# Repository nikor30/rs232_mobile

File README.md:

# RS232-WLAN-Konsole

Mobiler serieller Konsolenserver auf ESP32-Basis: mit dem WLAN-Hotspot des Geräts verbinden, `http://192.168.4.1` öffnen, Terminal auf Switch, Router oder Firewall. Keine App, kein Treiber, kein USB-Seriell-Adapter — und auf Wunsch aus der Ferne über die Leitstelle.

Firmware-Stand: **v1.8.2** · Board: **Waveshare ESP32-S3-Touch-LCD-2** · Oberflächen auf Englisch, Deutsch und Portugiesisch

## Was es kann

| Wo | Was |
|---|---|
| **Am Gerät** | Touch-Display mit Portstatus, Baudrate, Auto-Baud, BREAK, Terminal und Skripten; Akku mit Ladeanzeige und Sparmodus |
| **Im Browser** | xterm.js-Terminal über den eigenen Hotspot oder das Firmennetz, ohne Installation — am Handy wie am Notebook |
| **Im Netz** | Raw-TCP und Telnet je Port (PuTTY), Bluetooth-LE-Konsole, XMODEM/YMODEM, 802.1X (PEAP, TTLS, EAP-TLS), HTTPS |
| **Auf der SD-Karte** | Mitschnitte je Port, gespeicherte Konfigurationen zum Abspielen, verschlüsselte Sicherung; die Karte lässt sich als USB-Stick verleihen |
| **Aus der Ferne** | Leitstelle mit Geräteübersicht, Fernkonsole Ende-zu-Ende verschlüsselt, Firmware-Updates nur signiert (ML-DSA-65), Images auf die SD-Karte |

<table>
  <tr>
    <td align="center" width="38%"><br><sub>Touch-Display am Gerät</sub></td>
    <td align="center"><br><sub>Weboberfläche des Geräts am Handy</sub></td>
  </tr>
</table>

## Leitstelle

Geräte melden sich ausgehend per HTTPS bei einem Server — kein offener Port am Gerät, kein VPN. Der Kanal darin ist hybrid verschlüsselt (X25519 + ML-KEM-768); angemeldet wird mit einem sechsstelligen Code vom Display. Konten mit Passwort und Authenticator-App, Gruppen mit Rechten, Standorte, eine Bibliothek für Vorlagen, Firmware und Images.

Die **Fernkonsole** braucht einen Tipp am Gerät (oder eine dort gesetzte Frist für unbeaufsichtigten Zugriff), läuft höchstens 60 Minuten und ist Ende-zu-Ende verschlüsselt: Der Server trägt nur Chiffretext, Display und Browser zeigen denselben Code. Skripte lassen sich im Terminal abspielen, Sitzungen in eine Textdatei aufzeichnen.

## Hardware (Entwurf)

Eine Trägerplatine für das Waveshare-Modul mit **vier galvanisch getrennten RS232-Ports auf RJ45** (Cisco-Belegung; je Port Optokoppler, MAX3232E und eigener isolierter Wandler, aus dem Akku schaltbar) und ein druckbares Gehäuse. Entworfen und per KiCad-DRC geprüft, **noch nicht gebaut** — Quellen, Gerber für PCBWay und STL-Dateien im Zweig [`hardware-carrier`](../../tree/hardware-carrier/hardware).

<table>
  <tr>
    <td align="center"><br><sub>Trägerplatine 78 × 107 mm</sub></td>
    <td align="center"><br><sub>Körper, Platine, Boden</sub></td>
  </tr>
</table>

Heute läuft das Gerät mit einem MAX3232-Modul an einem Port, geprüft an Cisco C3750-X und C2960CX.

## Aufbau

- [`HANDOVER.md`](HANDOVER.md) — Projektstand, Erfahrungswissen, offene Punkte
- [`firmware/`](firmware/) — PlatformIO-Projekt für das Waveshare ESP32-S3-Touch-LCD-2 ([Weboberfläche und Netz](firmware/README.md), [Board](firmware/WAVESHARE.md))
- [`server/`](server/) — Leitstelle (Command-and-Control-Server) in Go: [Konzept](server/KONZEPT.md), [Betrieb und Admin-API](server/README.md)
- [`tests/`](tests/) — Host-Unittests der Firmware und Protokolltests gegen den Server

```bash
cd firmware
pio run -t upload                          # Englisch
pio run -e waveshare-s3-lcd2-de -t upload  # Deutsch (-pt: Portugiesisch)

cd server
docker compose up -d --build               # Leitstelle lokal, siehe server/README.md
```

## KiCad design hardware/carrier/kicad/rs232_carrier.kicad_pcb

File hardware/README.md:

# Hardware: Trägerplatine mit vier galvanisch getrennten RS232-Ports und Gehäuse

Stand 27. Oktober 2026, Revision 0.3 (Modul mittig, Gehäuse aus Körper und Boden) — **entworfen und per KiCad-DRC geprüft, noch nicht gebaut.**
Vor der Bestellung die Liste unter „Vor der Bestellung prüfen“ abarbeiten.

## Was es ist

Eine Trägerplatine (78 × 107 mm, zweilagig), auf die das **Waveshare ESP32-S3-Touch-LCD-2** mit seinen
beiden 14-poligen Stiftleisten gesteckt wird. Das Modul bringt Display, Touch, Lagesensor (QMI8658),
SD-Slot, LiPo-Lader und USB-C mit; die Trägerplatine ergänzt:

- **vier RS232-Ports auf RJ45** (Cisco-Konsolenbelegung: Pin 3 TX, Pin 6 RX, Pin 4/5 GND), jeder Port
  galvanisch getrennt — zwei Optokoppler **TLP2361** (10 MBd, einer je Richtung), ein **MAX3232E** und ein
  eigener isolierter 1-W-Wandler **B0505S-1WR3** (1,5 kV). Die vier Inseln sind auch voneinander getrennt.
- **Versorgung der Ports aus dem Akku**: VBAT → Aufwärtswandler MT3608 (5,1 V) → je Port ein High-Side-Schalter
  (2N7002 + AO3401), den die Firmware über GPIO16/17/18/10 schaltet. Ein abgeschalteter Port zieht nichts;
  ein eingeschalteter Port kostet rund 30–40 mA am Akku (Wandler im Leerlauf + MAX3232 + LED).
- **Lötbrücken** je Port, um TX/RX an der Buchse zu tauschen (JPx01/JPx02), und je Port eine Lötbrücke,
  ob der Port ohne Firmware-Unterstützung dauerhaft versorgt wird (JP11–JP14, Brücke 2-3 = immer an).
- Akku liegt **unter** der Trägerplatine im Gehäuse hinter einer Klappe und steckt an einer JST-PH-Buchse (J4) auf der
  Unterseite der Trägerplatine; BAT+ erreicht das Modul über Pin 14 (VBAT) der Stiftleiste. Falls dieser Pin nicht der
  Zellenanschluss ist (prüfen!), bleibt der Schlitz für ein Kabel zum MX1.25-Anschluss des Moduls.
- Stecker J3: 3V3, GND, I²C (GPIO47/48) und GPIO2/4/6 für spätere Erweiterungen.

Der Lagesensor für die automatische Drehung sitzt auf dem Modul; auf der Trägerplatine ist dafür nichts nötig.

### Externe Antenne

Das Modul hat eine Keramikantenne; das Bauteilfoto von Waveshare zeigt keine IPEX-Buchse, die
Schwesterboards haben eine mit 0-Ω-Umschaltwiderstand — am Modul nachsehen. Das Gehäuse hat links eine Bohrung (6,5 mm) für eine
RP-SMA-Einbaubuchse; ein U.FL/IPEX-Pigtail von dort zum Modul. **Am Modul nachsehen**, ob eine IPEX-Buchse
bestückt ist; wenn nicht, bleibt nur die Keramikantenne (das Gehäuse setzt sie an die linke, metallfreie Seite,
rund 50 mm von den RJ45-Buchsen entfernt).

## Verzeichnis

| Pfad | Inhalt |
|---|---|
| `carrier/generate.py` | **Die Quelle.** Erzeugt Schaltplan, Platine, Projekt, DRC-Regeln, `bom.csv` und `preview.png`. Alle Maße stehen hier (`VERIFY`, Platzierungen). |
| `carrier/kigen.py` | Schreiber für KiCad-7-Dateien (Symbole, Footprints, eingebettet — keine Bibliothek nötig) |
| `carrier/route.py` | Eigener Gitter-Autorouter (zwei Lagen, Vias, netzklassen-abhängige Abstände, Rip-up) |
| `carrier/drc.py` | Zonen füllen, KiCad-DRC, Fertigungsdaten exportieren (`kicad/fab/`) |
| `carrier/kicad/` | KiCad-7-Projekt: `rs232_carrier.kicad_pro/.kicad_sch/.kicad_pcb`, `channel.kicad_sch` (ein Port, viermal eingebunden), `.kicad_dru` |
| `carrier/kicad/fab/` | **Gerber + Bohrdaten als ZIP für PCBWay**, Bestückungsdaten (`-pos.csv`), Schaltplan-PDF, Platinen-PDF, DRC-Bericht |
| `carrier/bom.csv` | Stückliste mit Vorschlägen für Bauteile |
| `carrier/render3d.py` | Bestückte Platine als 3D-Ansicht von oben und unten (`kicad/fab/rs232_carrier-3d-*.png`), aus den Footprint-Maßen, ohne Herstellermodelle |
| `enclosure/generate_enclosure.py` | Erzeugt `rs232_console_case.scad` aus denselben Maßen und rendert die STL-Dateien |
| `enclosure/body.stl`, `base.stl` | Körper und Bodenplatte zum Drucken; `preview_*.png` zur Ansicht |

Neu erzeugen (KiCad 7 und OpenSCAD müssen installiert sein):

```bash
cd hardware/carrier && python3 generate.py && python3 route.py && python3 drc.py
cd ../enclosure && python3 generate_enclosure.py
```

`generate.py` ist deterministisch (feste UUIDs); Änderungen an Maßen oder Bauteilen dort eintragen, nicht in
den KiCad-Dateien — die werden überschrieben. Wer lieber in KiCad weiterarbeitet, nimmt die erzeugten Dateien
als Ausgangspunkt und lässt den Generator danach in Ruhe.

## Pinbelegung am Modul

| Port | RX (ESP-Eingang) | TX (ESP-Ausgang) | Versorgung an |
|---|---|---|---|
| 1 | GPIO44 | GPIO21 | GPIO16 |
| 2 | GPIO15 | GPIO13 | GPIO17 |
| 3 | GPIO11 | GPIO12 | GPIO18 |
| 4 | GPIO14 | GPIO9 | GPIO10 |

Port 1 behält die bisherige Belegung (RX 44 / TX 21). GPIO43 (U0TXD) bleibt frei, weil das ROM beim Reset dort
schreibt. Die TX-LED des Optokopplers liegt zwischen 3V3 und dem GPIO (Katode am GPIO): während des Resets ist
der Pin hochohmig, die LED aus, die RS232-Leitung in Ruhe — **beim Reset erscheint nichts auf dem Sendepin.**
Das Häkchen „RX/TX tauschen“ der Firmware darf mit dieser Platine nicht gesetzt werden (die Optokoppler haben
eine feste Richtung; 100 Ω in der RX-Leitung begrenzen den Strom, falls es doch passiert).

Firmware (geändert in diesem Stand, **nicht kompiliert und nicht am Gerät geprüft**):
`config.h` (Pin-Freigabe, `PINS_PORT_EN`), `serial_bridge.cpp/.h` (`portPower()`, `allPortsOff()`),
`lcd_ui.cpp` (Versorgungen vor dem Tiefschlaf aus und gehalten, nach dem Aufwachen freigegeben).
Ein aktivierter Port bekommt beim Start seine Versorgung, deaktivierte Ports bleiben stromlos.

## Signalweg eines Ports

```
ESP GPIO (TX) ─330Ω/LED─▶ TLP2361 ─▶ T1IN  MAX3232E  T1OUT ─JP01─▶ RJ45 Pin 3
ESP GPIO (RX) ◀─100Ω──── TLP2361 ◀─ 74LVC1G17 ◀─ R1OUT   R1IN ◀─JP02─ RJ45 Pin 6
                 3V3-Seite  ║ 1,5 kV ║  ISO5V-Seite (B0505S aus dem geschalteten 5 V)
```

Beide LEDs sind in Ruhe (UART-Mark) aus, also kein Ruhestrom durch die Koppler. Der Schmitt-Puffer treibt die
RX-LED, weil der Empfängerausgang des MAX3232 dafür zu schwach ist.

## Mechanik und Gestaltung

Leitlinie (Rams, Ive): ein ruhiger Körper mit durchlaufenden Radien, symmetrische Flächen, außen nur, was
täglich gebraucht wird, keine sichtbaren Schrauben, Fugen nur dort, wo man sie nicht sieht.

- Modul **hochkant und mittig** auf der Trägerplatine, 11 mm darüber: USB-C in der Mitte der oberen Stirnseite,
  die Nadellöcher für BOOT/RST symmetrisch daneben, die Antenne des Moduls zeigt zu den Ports. Links vom Modul
  der Aufwärtswandler mit den Entkoppeldioden, rechts die vier Portschalter, darunter die vier Inseln und die
  RJ45-Reihe — die Platine ist um ihre Mittellinie symmetrisch aufgeteilt.
- **Das Displayglas ist die Oberseite** (bündig, 0,15 mm Spiel im Rahmen; der Rahmen ist zur USB-C-Seite
  offen, die Stirnwand liegt unter dem Glasüberstand). Über den Buchsen sind die Ziffern 1–4 in die Oberseite
  vertieft (0,4 mm) — die einzige Beschriftung.
- **Zwei gedruckte Teile, keine Schraube** (`enclosure/`):
  - `body.stl` — der ganze Körper: Oberseite mit Glasrahmen und alle vier Wände bis zur Unterkante, Ecken
    R 5, Kanten R 1,2. Öffnungen: vier geschlossene Fenster für die RJ45 (die Buchsen sitzen 0,6 mm hinter
    der Platinenkante, also ganz in der Wand), eine Mulde für USB-C, zwei Nadellöcher (1,5 mm), die
    RP-SMA-Bohrung rechts oben an der Seitenwand. Innen vier Pfosten, die die Trägerplatine auf die Zapfen
    des Bodens drücken, und eine Nut, in die die Haken des Bodens greifen.
  - `base.stl` — Bodenplatte, **liegt innen in den Wänden**, 0,6 mm zurückgesetzt: die Fuge ist nur von unten
    zu sehen. Sechs Rasthaken (10 × 1,6 × 6 mm, 0,8 mm Nase, 30° Einführ-, 45° Haltewinkel, Wurzelradius
    0,8 mm) klicken in die Nut; zwei Kerben in der Unterkante nehmen einen Fingernagel oder Spatel zum Öffnen.
    Acht Zapfen tragen die Trägerplatine (Schulter 5,5 mm, Stift 2,4 bzw. 1,9 mm durch die Bohrungen),
    ein 1,5 mm hoher Rahmen hält den Akku (bis 60 × 70 × 6 mm) an seinem Platz, vier Vertiefungen für
    8-mm-Gummifüße, Schriftzug vertieft. Boden abziehen = Akku wechseln (Stecker J4 auf der Unterseite der
    Trägerplatine), ohne Werkzeug.
- Einbau: Trägerplatine mit Modul von unten in den Körper schieben (die Buchsen fahren in ihre Fenster, das
  Glas in den Rahmen), Boden mit Akku aufsetzen, bis die sechs Haken klicken.
- Nicht nach außen geführt: der SD-Slot (sitzt beim mittigen Modul 22 mm von der Wand; die Karte bleibt
  eingebaut, Zugriff über den USB-Stick-Modus oder nach Abnehmen des Bodens).
- Außen **83 × 114 × 31 mm**. Drucken: Körper mit der Oberseite nach unten (Pfosten wachsen nach oben, der
  Glasrahmen wird glatt), Boden flach (Haken wachsen nach oben); PETG oder ABS, nicht PLA. Farbe nach Rams:
  helles Warmgrau oder Anthrazit, matt. Regeln aus den FDM-Leitfäden (Hubs, Formlabs, Core77): Spiel 0,3 mm,
  Hakenlänge ≈ 4 × Dicke mit Wurzelradius, in Z gedruckte Haken dicker als flach gedruckte. **Erster Druck als
  Probe**: Haken und Nut sind nicht gedruckt worden; Spiel ggf. in `generate_enclosure.py` (`clr`,
  `hook_catch`) anpassen.
- Isolationsabstand auf der Platine: 5 mm kupferfreies Band zwischen ESP-Seite und Inseln (DRC-Regel 3 mm),
  1,8 mm zwischen den Inseln (DRC-Regel 1,5 mm). Unter den Zapfen/Pfosten ist das Kupfer ausgespart.

## Bestellen bei PCBWay

Datei `carrier/kicad/fab/rs232_carrier-gerbers-pcbway.zip` hochladen. Einstellungen: 2 Lagen, 78 × 107 mm,
FR-4 1,6 mm, 1 oz Kupfer, Lötstopplack beliebig, HASL bleifrei oder ENIG, kleinste Leiterbahn/Abstand
0,25/0,2 mm (Mindestwerte der Platine: 0,25 mm Bahn, 0,2 mm Abstand, Via 0,7/0,3 mm). Keine besonderen
Anforderungen. Für Bestückung durch PCBWay: `rs232_carrier-pos.csv` und `bom.csv` (Bauteile dort ergänzen).

## Vor der Bestellung prüfen

Die Maße des Waveshare-Moduls stammen aus der offiziellen Maßzeichnung (Platine 35,00 × 48,20 mm, vier
Bohrungen 29,00 × 42,20 mm im Abstand 3,00 mm von den Kanten, Glas 37,10 × 58,80 mm mit R2,60, Stapel
9,70 mm gesamt bzw. 7,20 mm von der Glasoberseite bis zur Platinenunterseite, Stiftleisten 30,48 mm
auseinander, USB-C mittig). Alles steht in `carrier/generate.py` unter `VERIFY`; nach einer Korrektur die
drei Skripte neu laufen lassen.

1. **Lage von Pin 1** der Stiftleisten in Längsrichtung (7,3 mm vom USB-C-fernen Rand, aus der Zeichnung
   abgeleitet, nicht bemaßt). Ein Fehler von mehr als 0,3 mm und das Modul passt nicht in die Buchsen —
   vor dem Einlöten der Buchsenleisten mit dem Modul abgleichen.
2. **Glasüberstand**: Das Glas (58,80 mm) ist 10,6 mm länger als die Platine (48,20 mm); angenommen ist je
   5,3 mm Überstand an beiden kurzen Seiten und 1,05 mm an den langen. Die Zeichnung bemaßt den Überstand
   nicht getrennt — am Modul nachmessen, sonst stimmt das Gehäusefenster nicht.
3. **Stapelhöhe** 11 mm (Buchsenleiste 8,5 mm + Stiftleistenkörper 2,5 mm) und Glasoberkante 5,6 mm über
   der Modulplatine (7,20 − 1,60 aus der Seitenansicht). Bestimmt, ob das Glas bündig mit dem Körper
   abschließt; mit 1-mm-Unterlegscheiben unter den Buchsenleisten lässt sich das ausgleichen.
4. **RJ45-Buchse**: Der Footprint `RJ45_Generic` ist ein Platzhalter (Pins 1,27 mm Raster, zwei Reihen 2,54 mm,
   Zapfen 3,25 mm im Abstand 11,43 mm). Vor der Bestellung die Buchse festlegen (z. B. Amphenol 54602-908LF
   oder RJHSE-5380) und den Footprint in `generate.py` an deren Datenblatt anpassen — oder in KiCad den
   Bibliotheks-Footprint zuweisen. Pin 1 ist links, wenn man von vorn in die Buchse sieht, die Rastnase unten.
5. **B0505S-1WR3**: Pins auf 0 / 2,54 / 10,16 / 12,7 mm, Pin 1 = −Vin. Im Datenblatt gegenprüfen.
6. **TLP2361**: Pin 1 Anode, 3 Katode, 4 GND, 5 Ausgang, 6 Vcc (Pin 2 fehlt). Ebenso für ACPL-M61L.
   LED-Vorwiderstände (330 Ω / 680 Ω ≈ 5 mA) an den gewählten Typ anpassen.
7. **MT3608**: Vout = 0,6 V · (1 + 75k/10k) = 5,1 V — innerhalb der 4,5–5,5 V des B0505S.
8. **Spule** L1: Footprint ist ein generisches 5 × 5 mm mit zwei Pads; Bauteil mit ≥ 1 A Sättigungsstrom.
9. **Antenne**: IPEX-Buchse am Modul vorhanden? Sonst SMA-Bohrung verschließen.
10. **VBAT an Pin 14 der Stiftleiste**: Mit dem Multimeter prüfen, dass der Pin direkt mit BAT+ des MX1.25-Anschlusses
    verbunden ist (0 Ω). Nur dann lädt und versorgt der Akku an J4 das Modul über die Stiftleiste. Sonst ein kurzes
    Kabel von J4 durch den Schlitz zum MX1.25-Anschluss ziehen und J4 nicht bestücken.
11. **USB-C-Überstand** des Moduls (angenommen 1,9 mm über die Platinenkante) — bestimmt den Abstand der
    Stirnwand zur Modulkante.

Was sonst noch offen ist: Die Firmwareänderung ist ungetestet (kein PlatformIO in der Sandbox); die
Optokoppler-Schaltung ist nach Datenblattwerten ausgelegt, nicht gemessen; der Autorouter hat keine
Längen- oder Impedanzregeln (bei 115 200 Baud belanglos). Die Silkscreen-Warnungen des DRC (Texte
überlappen Bauteilumrisse) sind kosmetisch.

## Entscheidungen

- **Trägerplatine statt eigener Hauptplatine**: Die Firmware ist auf dieses Modul (Display, Touch, SD,
  Lagesensor, Lader) eingerichtet; ein Nachbau dieser Funktionen auf einer eigenen Platine wäre ein
  Vielfaches an Aufwand ohne Nutzen. Nachteil: die Antenne bleibt die des Moduls.
- **RJ45 statt DB9**: Vier DB9 wären 130 mm breit. Mit der Cisco-Belegung passt das vorhandene blaue
  Rollover-Kabel direkt an Cisco/HP/Juniper-Konsolen; an DB9-Geräte kommt man mit dem üblichen
  RJ45-DB9-Adapter des Kabelsatzes. Wer eine andere Belegung braucht, lötet JPx01/JPx02 um.
- **Optokoppler statt digitaler Isolatoren** (Wunsch): TLP2361 ist mit 10 MBd und 2,7–5,5 V Versorgung
  für beide Seiten geeignet; ein ADuM1201 wäre kleiner und ohne LED-Strom, aber eine andere Schaltung.
- **Ein Wandler je Port** statt einem gemeinsamen: nur so sind die Ports auch untereinander getrennt
  (zwei Geräte mit verschiedenem Erdpotential gleichzeitig).
- **Schaltbare Versorgung**: Die vier Wandler zögen sonst dauerhaft 30–60 mA; am 1000-mAh-Akku wären das
  Stunden. Standard ist „aus“ (Pull-down), die Firmware schaltet ein.
- **Abstände**: 19 mm Portraster, weil 17,5/18 mm für Ladungspumpen-Kondensatoren, MAX3232 und Wandler in
  einer Spalte nicht reichten — die Platine wurde dafür von 72 auf 78 mm breiter; mit dem hochkant stehenden
  Modul (Wunsch: USB-C an der Stirnseite, Glas als Oberseite) 107 mm lang.
- **Zusammenstecken statt Schrauben** (Wunsch): Körper und innenliegender Boden mit sechs lösbaren Haken; die
  Trägerplatine ist zwischen Zapfen und Pfosten geklemmt. Boden ab = Akku zugänglich (J4 auf der Platinenunterseite).
- **Modul mittig** (Wunsch): Versorgung links und rechts aufgeteilt; dafür ist der SD-Slot nicht mehr von außen
  erreichbar — die Karte bleibt eingebaut.

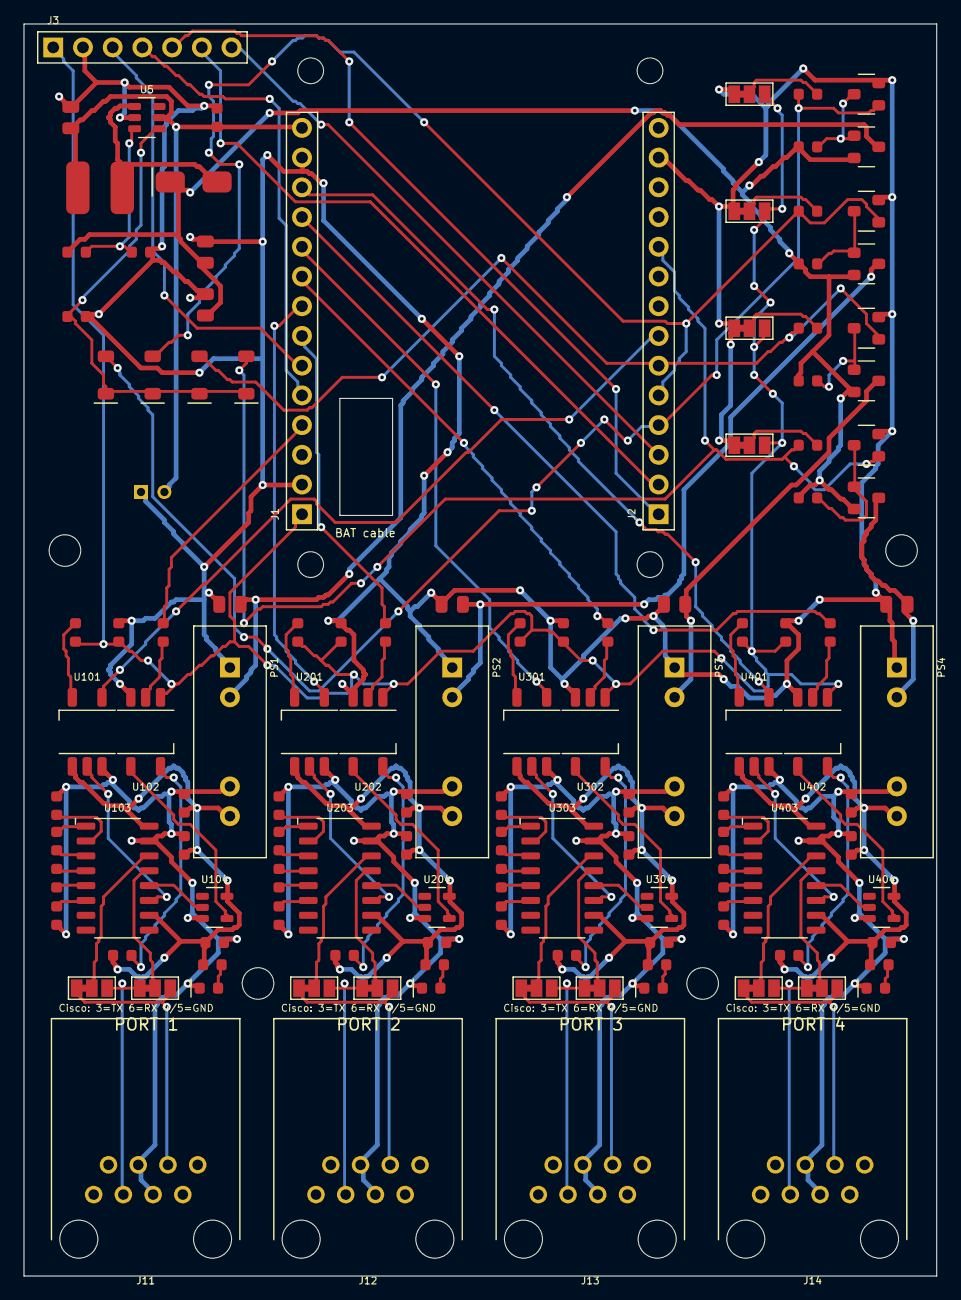
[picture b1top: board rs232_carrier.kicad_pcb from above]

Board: 2 copper layers, 78.0 x 107.0 mm, 134 parts (1 on the bottom side), 112 nets.

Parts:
C51: 10u; C_0805
C52, C53: 22u; C_0805
C54, C101, C102, C103, C104, C105, C107, C108, C201, C202, C203, C204, C205, C207, C208, C301, C302, C303, C304, C305, C307, C308, C401, C402, C403, C404, C405, C407, C408: 100n; C_0603
C109, C209, C309, C409: 4.7u; C_0603
C110, C210, C310, C410: 2.2u; C_0805
D5: SS14; D_SMA
D51, D52, D53, D54: 1N4148W; D_SOD-123
D101, D201, D301, D401: LED green; LED_0603
H1, H2, H3, H4: M2 Waveshare; MountingHole_2.2
H5, H6, H7, H8: M2.5 enclosure; MountingHole_2.7
J1: WS header 1-14; PinSocket_1x14
J2: WS header 15-28; PinSocket_1x14_B
J3: EXT; PinHeader_1x7
J4: BAT JST-PH; JST_PH_2_Vertical
J11, J12, J13, J14: RJ45; RJ45_Generic
JP11: EN1 dflt; SolderJumper_3_Bridged12
JP12: EN2 dflt; SolderJumper_3_Bridged12
JP13: EN3 dflt; SolderJumper_3_Bridged12
JP14: EN4 dflt; SolderJumper_3_Bridged12
JP101, JP201, JP301, JP401: TX->3; SolderJumper_3_Bridged12
JP102, JP202, JP302, JP402: RX<-6; SolderJumper_3_Bridged12
L1: 22u; L_5x5
PS1, PS2, PS3, PS4: B0505S-1WR3; SIP-4_DCDC
Q11, Q21, Q31, Q41: 2N7002; SOT-23
Q12, Q22, Q32, Q42: AO3401A; SOT-23
R51: 75k; R_0603
R52, R61, R62, R63, R64: 10k; R_0603
R53, R71, R72, R73, R74: 100k; R_0603
R101, R201, R301, R401: 330; R_0603
R102, R202, R302, R402: 680; R_0603
R103, R203, R303, R403: 100; R_0603
R104, R204, R304, R404: 2k2; R_0603
U5: MT3608; SOT-23-6
U101, U102, U201, U202, U301, U302, U401, U402: TLP2361; SO6_Opto
U103, U203, U303, U403: MAX3232E; SOIC-16
U104, U204, U304, U404: 74LVC1G17; SOT-23-5

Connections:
+3V3: C107.1, C207.1, C307.1, C407.1, J1.1, J3.1, JP11.3, JP12.3, JP13.3, JP14.3, R101.1, R201.1, R301.1, R401.1, U102.6, U202.6, U302.6, U402.6
+5V: C52.1, C53.1, D5.1, Q12.2, Q22.2, Q32.2, Q42.2, R51.1, R71.1, R72.1, R73.1, R74.1
/CH1/BUF_OUT: U102.3, U104.4
/CH1/C1N: C101.2, U103.3
/CH1/C1P: C101.1, U103.1
/CH1/C2N: C102.2, U103.5
/CH1/C2P: C102.1, U103.4
/CH1/ISO5V: C105.1, C108.1, C109.1, PS1.4, R102.1, R104.1, U101.6, U103.10, U103.16, U104.5
/CH1/ISOGND: C103.2, C104.2, C105.2, C108.2, C109.2, D101.1, J11.4, J11.5, PS1.3, U101.4, U103.15, U104.3
/CH1/LEDA: D101.2, R104.2
/CH1/R1IN: JP102.2, U103.13
/CH1/R1OUT: U103.12, U104.2
/CH1/RJ3: J11.3, JP101.1, JP102.3
/CH1/RJ6: J11.6, JP101.3, JP102.1
/CH1/RXA: R102.2, U102.1
/CH1/RX_O: R103.1, U102.5
/CH1/T1IN: U101.5, U103.11
/CH1/T1OUT: JP101.2, U103.14
/CH1/TXA: R101.2, U101.1
/CH1/VN: C104.1, U103.6
/CH1/VP: C103.1, U103.2
/CH2/BUF_OUT: U202.3, U204.4
/CH2/C1N: C201.2, U203.3
/CH2/C1P: C201.1, U203.1
/CH2/C2N: C202.2, U203.5
/CH2/C2P: C202.1, U203.4
/CH2/ISO5V: C205.1, C208.1, C209.1, PS2.4, R202.1, R204.1, U201.6, U203.10, U203.16, U204.5
/CH2/ISOGND: C203.2, C204.2, C205.2, C208.2, C209.2, D201.1, J12.4, J12.5, PS2.3, U201.4, U203.15, U204.3
/CH2/LEDA: D201.2, R204.2
/CH2/R1IN: JP202.2, U203.13
/CH2/R1OUT: U203.12, U204.2
/CH2/RJ3: J12.3, JP201.1, JP202.3
/CH2/RJ6: J12.6, JP201.3, JP202.1
/CH2/RXA: R202.2, U202.1
/CH2/RX_O: R203.1, U202.5
/CH2/T1IN: U201.5, U203.11
/CH2/T1OUT: JP201.2, U203.14
/CH2/TXA: R201.2, U201.1
/CH2/VN: C204.1, U203.6
/CH2/VP: C203.1, U203.2
/CH3/BUF_OUT: U302.3, U304.4
/CH3/C1N: C301.2, U303.3
/CH3/C1P: C301.1, U303.1
/CH3/C2N: C302.2, U303.5
/CH3/C2P: C302.1, U303.4
/CH3/ISO5V: C305.1, C308.1, C309.1, PS3.4, R302.1, R304.1, U301.6, U303.10, U303.16, U304.5
/CH3/ISOGND: C303.2, C304.2, C305.2, C308.2, C309.2, D301.1, J13.4, J13.5, PS3.3, U301.4, U303.15, U304.3
/CH3/LEDA: D301.2, R304.2
/CH3/R1IN: JP302.2, U303.13
/CH3/R1OUT: U303.12, U304.2
/CH3/RJ3: J13.3, JP301.1, JP302.3
/CH3/RJ6: J13.6, JP301.3, JP302.1
/CH3/RXA: R302.2, U302.1
/CH3/RX_O: R303.1, U302.5
/CH3/T1IN: U301.5, U303.11
/CH3/T1OUT: JP301.2, U303.14
/CH3/TXA: R301.2, U301.1
/CH3/VN: C304.1, U303.6
/CH3/VP: C303.1, U303.2
/CH4/BUF_OUT: U402.3, U404.4
/CH4/C1N: C401.2, U403.3
/CH4/C1P: C401.1, U403.1
/CH4/C2N: C402.2, U403.5
/CH4/C2P: C402.1, U403.4
/CH4/ISO5V: C405.1, C408.1, C409.1, PS4.4, R402.1, R404.1, U401.6, U403.10, U403.16, U404.5
/CH4/ISOGND: C403.2, C404.2, C405.2, C408.2, C409.2, D401.1, J14.4, J14.5, PS4.3, U401.4, U403.15, U404.3
/CH4/LEDA: D401.2, R404.2
/CH4/R1IN: JP402.2, U403.13
/CH4/R1OUT: U403.12, U404.2
/CH4/RJ3: J14.3, JP401.1, JP402.3
/CH4/RJ6: J14.6, JP401.3, JP402.1
/CH4/RXA: R402.2, U402.1
/CH4/RX_O: R403.1, U402.5
/CH4/T1IN: U401.5, U403.11
/CH4/T1OUT: JP401.2, U403.14
/CH4/TXA: R401.2, U401.1
/CH4/VN: C404.1, U403.6
/CH4/VP: C403.1, U403.2
EN1: D51.2, J2.25, Q11.1, R61.1
EN2: D52.2, J2.24, Q21.1, R62.1
EN3: D53.2, J2.23, Q31.1, R63.1
EN4: D54.2, J2.19, Q41.1, R64.1
ENP1: JP11.2, R61.2
ENP2: JP12.2, R62.2
ENP3: JP13.2, R63.2
ENP4: JP14.2, R64.2
ESP_RX1: J1.4, R103.2
ESP_RX2: J1.7, R203.2
ESP_RX3: J1.9, R303.2
ESP_RX4: J1.11, R403.2
ESP_TX1: J2.22, U101.3
ESP_TX2: J1.8, U201.3
ESP_TX3: J1.10, U301.3
ESP_TX4: J1.12, U401.3
FB: R51.2, R52.1, U5.3
GND: C51.2, C52.2, C53.2, C54.2, C107.2, C110.2, C207.2, C210.2, C307.2, C310.2, C407.2, C410.2, J1.2, J1.13, J2.16, J3.2, J4.1, JP11.1, JP12.1, JP13.1, JP14.1, PS1.1, PS2.1, PS3.1, PS4.1, Q11.2, Q21.2, Q31.2, Q41.2, R52.2, R53.2, U5.2, U102.4, U202.4, U302.4, U402.4
IO2: J2.28, J3.5
IO4: J2.27, J3.6
IO6: J2.26, J3.7
ISO_IN1: C110.1, PS1.2, Q12.3
ISO_IN2: C210.1, PS2.2, Q22.3
ISO_IN3: C310.1, PS3.2, Q32.3
ISO_IN4: C410.1, PS4.2, Q42.3
PG1: Q11.3, Q12.1, R71.2
PG2: Q21.3, Q22.1, R72.2
PG3: Q31.3, Q32.1, R73.2
PG4: Q41.3, Q42.1, R74.2
PWR_EN: D51.1, D52.1, D53.1, D54.1, R53.1, U5.4
SCL: J1.5, J3.4
SDA: J1.6, J3.3
SW: D5.2, L1.2, U5.1
VBAT: C51.1, C54.1, J1.14, J4.2, L1.1, U5.5

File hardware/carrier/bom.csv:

refs,qty,value,footprint,suggested part,note
C54 C101 C102 C103 C104 C105 C107 C108 C201 C202 C203 C204 C205 C207 C208 C301 C302 C303 C304 C305 C307 C308 C401 C402 C403 C404 C405 C407 C408,29,100n,C_0603,100n 0603 X7R/X5R >=10 V,ceramic
C109 C209 C309 C409,4,4.7u,C_0603,4.7u 0603 X7R/X5R >=10 V,ceramic
C51,1,10u,C_0805,10u 0805 X7R/X5R >=10 V,ceramic
C110 C210 C310 C410,4,2.2u,C_0805,2.2u 0805 X7R/X5R >=10 V,ceramic
C52 C53,2,22u,C_0805,22u 0805 X7R/X5R >=10 V,ceramic
D5,1,SS14,D_SMA,Vishay SS14,"40 V Schottky, SMA"
D51 D52 D53 D54,4,1N4148W,D_SOD-123,Diodes Inc 1N4148W-7-F,
J4,1,BAT JST-PH,JST_PH_2_Vertical,,
D101 D201 D301 D401,4,LED green,LED_0603,Everlight 19-217/GHC-YR1S2/3T,"any 0603 green LED, cathode mark"
L1,1,22u,L_5x5,Bourns SRN5040-220M,"22 uH, >=1 A sat; any 4x4..5x5 mm shielded inductor with 2 pads"
J3,1,EXT,PinHeader_1x7,1x7 pin header 2.54 mm,optional
J1,1,WS header 1-14,PinSocket_1x14,"1x14 socket 2.54 mm, 8.5 mm","female header, the Waveshare module plugs in"
J2,1,WS header 15-28,PinSocket_1x14_B,"1x14 socket 2.54 mm, 8.5 mm",female header
J11 J12 J13 J14,4,RJ45,RJ45_Generic,Amphenol 54602-908LF,"8P8C tab-down, no magnetics, no LEDs; footprint must match the chosen part"
R103 R203 R303 R403,4,100,R_0603,100 0603 1%,
R53 R71 R72 R73 R74,5,100k,R_0603,100k 0603 1%,
R52 R61 R62 R63 R64,5,10k,R_0603,10k 0603 1%,
R104 R204 R304 R404,4,2k2,R_0603,2k2 0603 1%,
R101 R201 R301 R401,4,330,R_0603,330 0603 1%,
R102 R202 R302 R402,4,680,R_0603,680 0603 1%,
R51,1,75k,R_0603,75k 0603 1%,
PS1 PS2 PS3 PS4,4,B0505S-1WR3,SIP-4_DCDC,Mornsun B0505S-1WR3,"alt. Hi-Link B0505S-1WR3, Mean Well SPU01L-05; verify pin spacing 2.54/7.62"
U101 U102 U201 U202 U301 U302 U401 U402,8,TLP2361,SO6_Opto,"Toshiba TLP2361(E,T)","alt. Broadcom ACPL-M61L-000E (same pinout); 10 Mbd, 2.7-5.5 V"
U103 U203 U303 U403,4,MAX3232E,SOIC-16,TI MAX3232ECDR,"alt. Maxim MAX3232ECSE+, Exar SP3232EEN-L; ESD-protected version"
Q11 Q21 Q31 Q41,4,2N7002,SOT-23,"Nexperia 2N7002,215",
Q12 Q22 Q32 Q42,4,AO3401A,SOT-23,Alpha&Omega AO3401A,P-channel high-side switch
U104 U204 U304 U404,4,74LVC1G17,SOT-23-5,TI SN74LVC1G17DBVR,alt. Nexperia 74LVC1G17GV; Schmitt buffer drives the RX LED
U5,1,MT3608,SOT-23-6,Aerosemi MT3608,boost VBAT -> 5.1 V; alt. TPS61023 (different footprint)

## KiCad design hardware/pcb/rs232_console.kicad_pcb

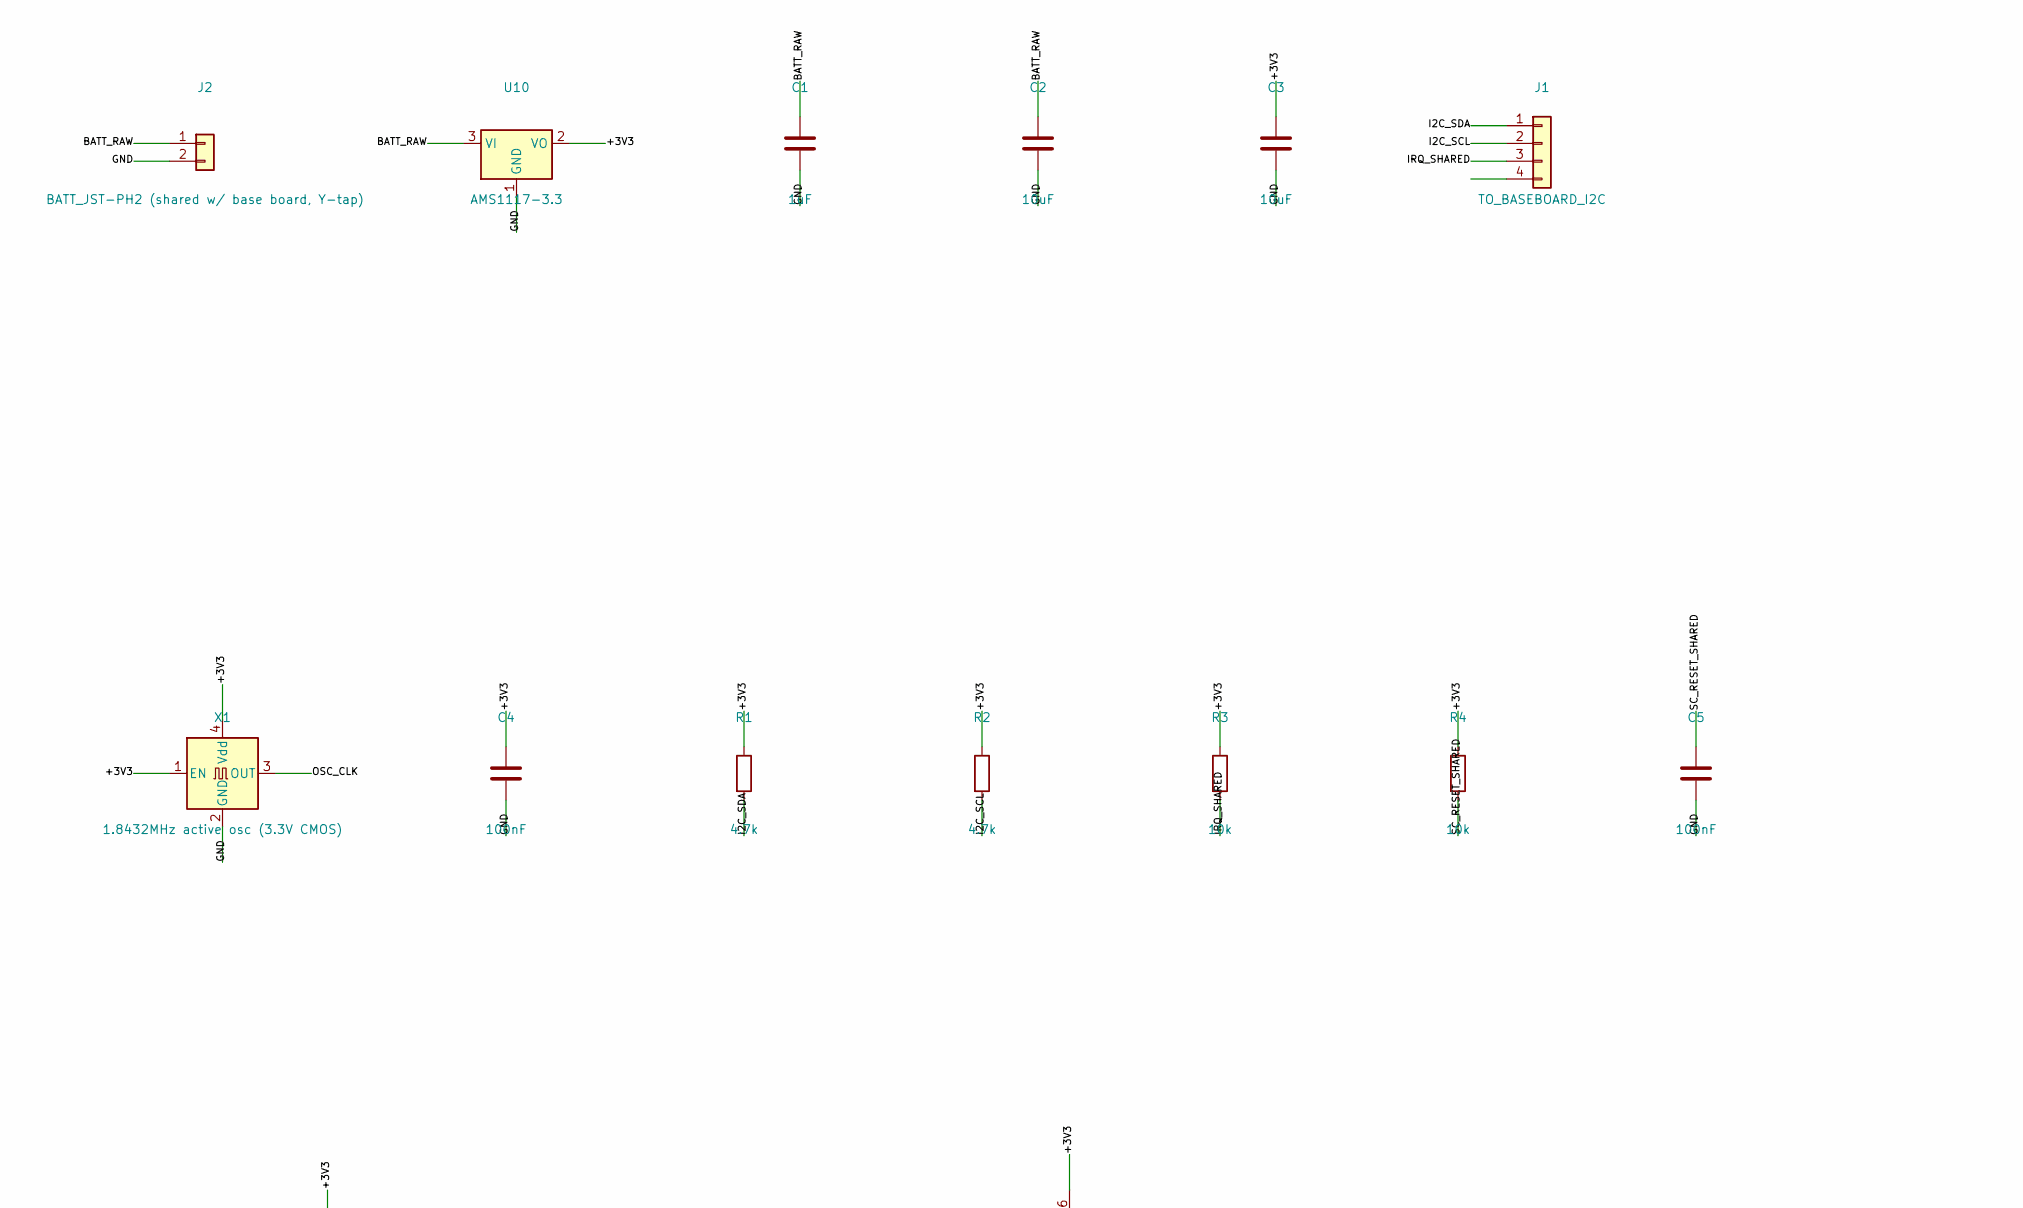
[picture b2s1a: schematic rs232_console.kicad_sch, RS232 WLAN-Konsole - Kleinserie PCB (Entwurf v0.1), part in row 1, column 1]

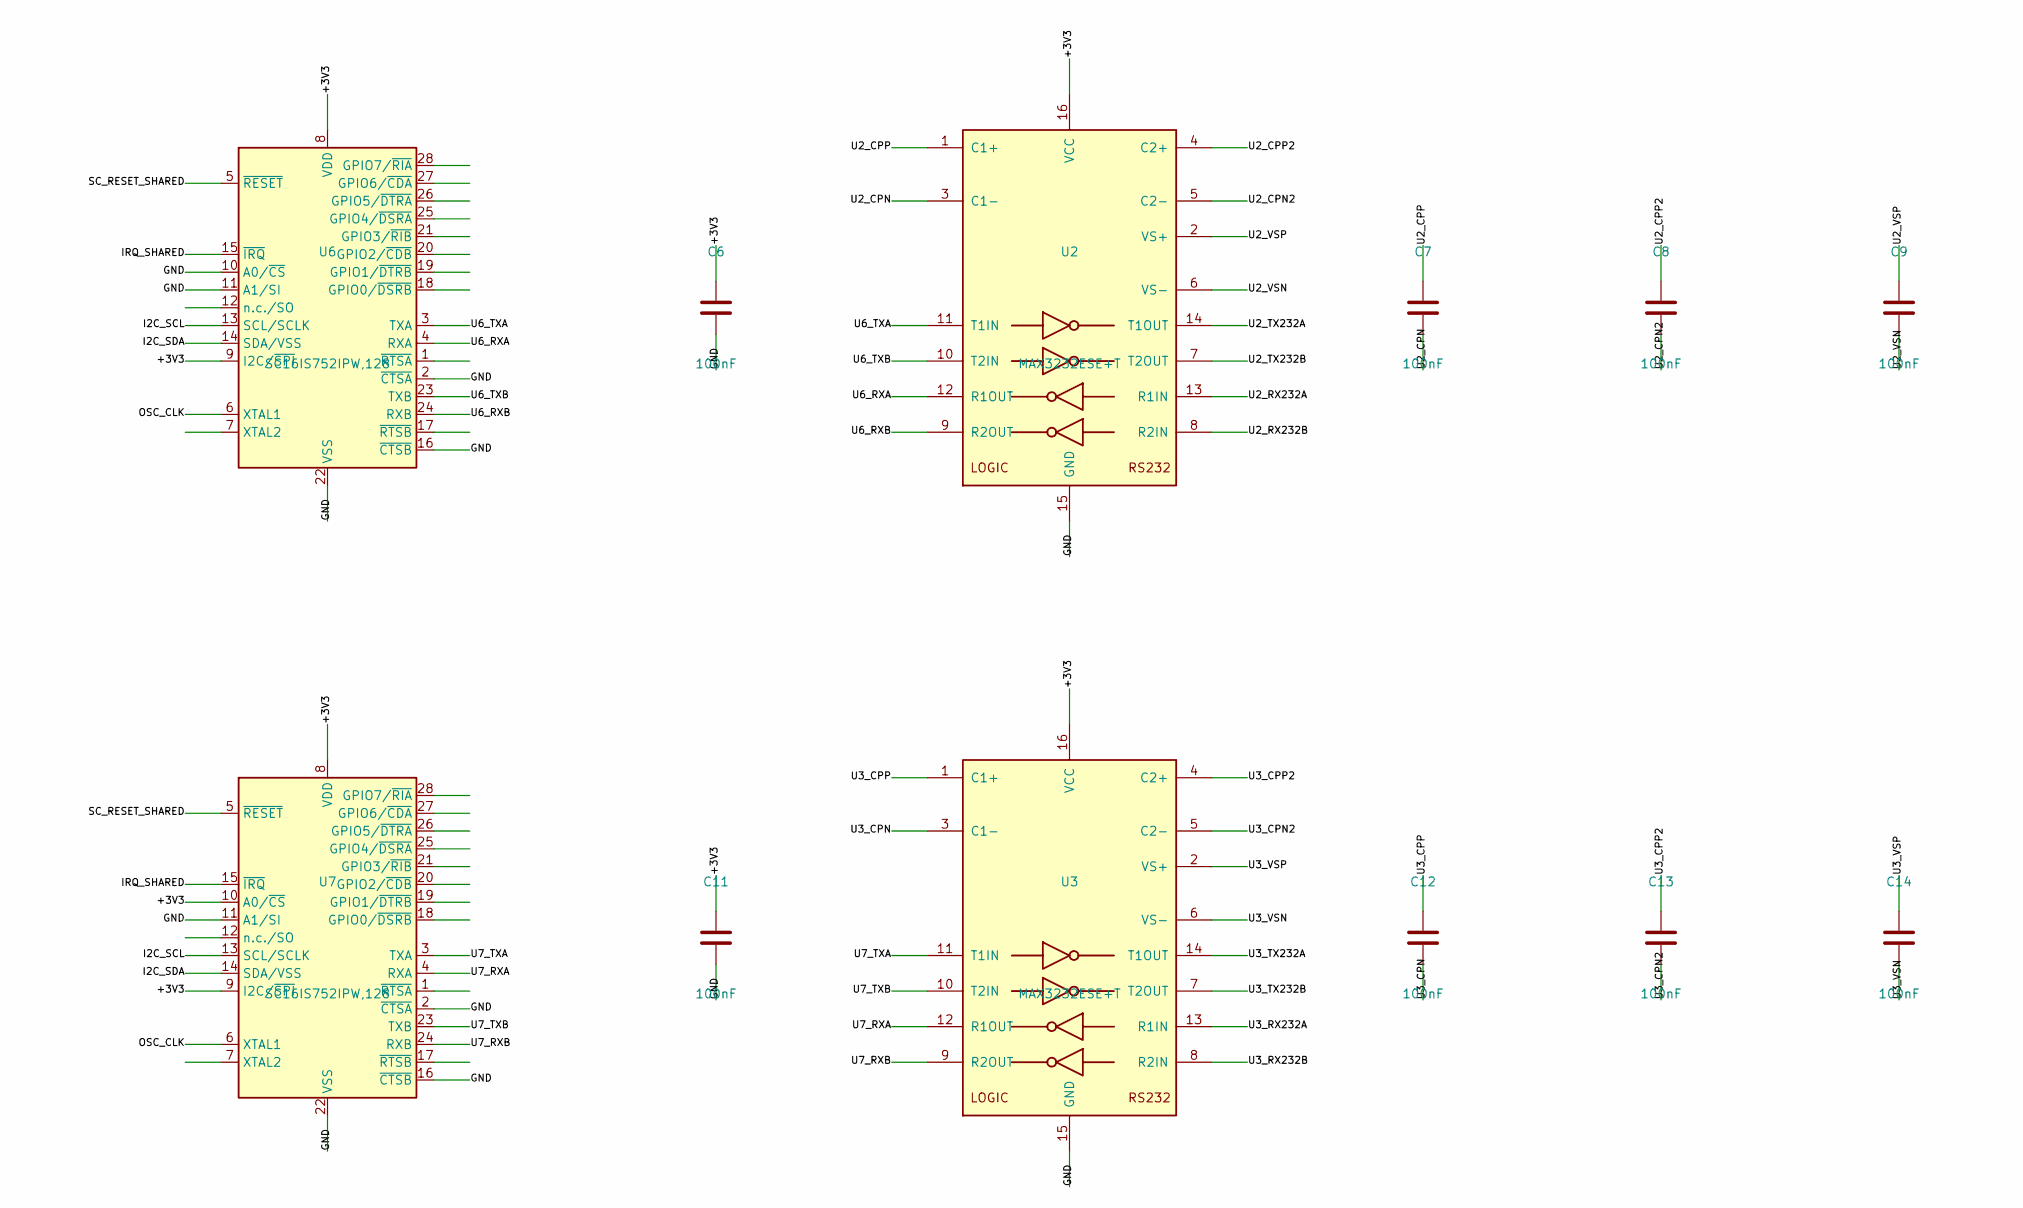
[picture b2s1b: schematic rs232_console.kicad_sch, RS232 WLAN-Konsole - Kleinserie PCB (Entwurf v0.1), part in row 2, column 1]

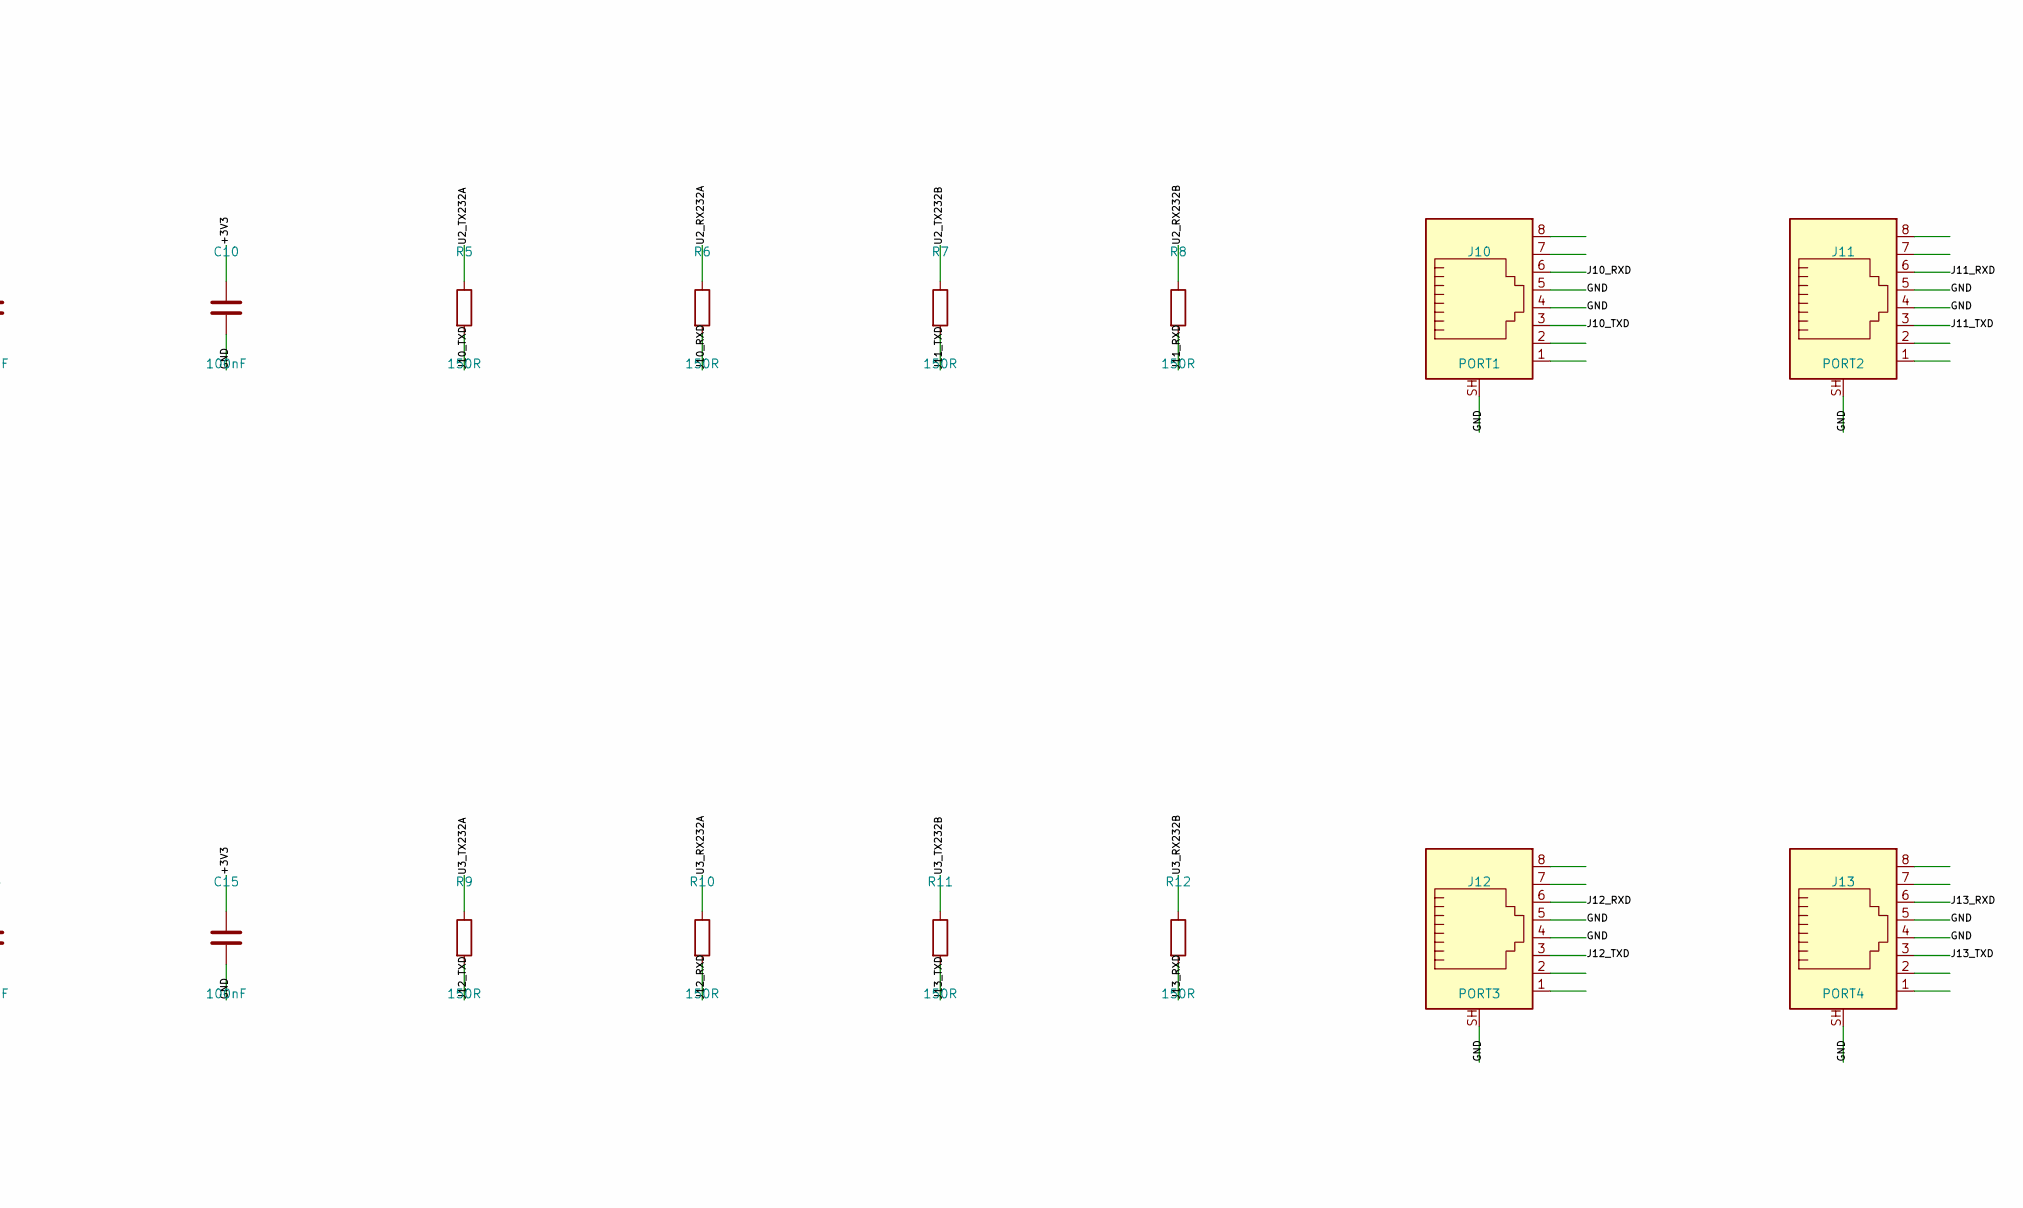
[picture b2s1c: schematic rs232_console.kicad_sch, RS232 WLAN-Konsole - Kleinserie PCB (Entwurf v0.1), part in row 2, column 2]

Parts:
C1: 1uF; C_0805_2012Metric
C2, C3: 10uF; C_0805_2012Metric
C4, C5, C6, C7, C8, C9, C10, C11, C12, C13, C14, C15: 100nF; C_0805_2012Metric
J1: TO_BASEBOARD_I2C; JST_SH_BM04B-SRSS-TB_1x04-1MP_P1.00mm_Vertical
J2: BATT_JST-PH2 (shared w/ base board, Y-tap); PinHeader_1x02_P2.54mm_Vertical
J10: PORT1; RJ45_Amphenol_RJHSE5380
J11: PORT2; RJ45_Amphenol_RJHSE5380
J12: PORT3; RJ45_Amphenol_RJHSE5380
J13: PORT4; RJ45_Amphenol_RJHSE5380
R1, R2: 4.7k; R_0805_2012Metric
R3, R4: 10k; R_0805_2012Metric
R5, R6, R7, R8, R9, R10, R11, R12: 150R; R_0805_2012Metric
U2, U3: MAX3232ESE+T; SOIC-16_3.9x9.9mm_P1.27mm
U6, U7: SC16IS752IPW,128; TSSOP-28_4.4x9.7mm_P0.65mm
U10: AMS1117-3.3; SOT-223-3_TabPin2
X1: 1.8432MHz active osc (3.3V CMOS); Oscillator_SMD_Abracon_ASE-4Pin_3.2x2.5mm

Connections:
+3V3: C3.1, C4.1, C6.1, C10.1, C11.1, C15.1, R1.1, R2.1, R3.1, R4.1, U2.16 (VCC), U3.16 (VCC), U6.8 (VDD), U6.9 (I2C/~SPI), U7.8 (VDD), U7.9 (I2C/~SPI), U7.10 (A0/~CS), U10.2 (VO), X1.1 (EN), X1.4 (Vdd)
BATT_RAW: C1.1, C2.1, J2.1, U10.3 (VI)
GND: C1.2, C2.2, C3.2, C4.2, C5.2, C6.2, C10.2, C11.2, C15.2, J2.2, J10.4, J10.5, J10.SH, J11.4, J11.5, J11.SH, J12.4, J12.5, J12.SH, J13.4, J13.5, J13.SH, U2.15 (GND), U3.15 (GND), U6.2 (~CTSA), U6.10 (A0/~CS), U6.11 (A1/SI), U6.16 (~CTSB), U6.22 (VSS), U7.2 (~CTSA), U7.11 (A1/SI), U7.16 (~CTSB), U7.22 (VSS), U10.1 (GND), X1.2 (GND)
I2C_SCL: J1.2, R2.2, U6.13 (SCL/SCLK), U7.13 (SCL/SCLK)
I2C_SDA: J1.1, R1.2, U6.14 (SDA/VSS), U7.14 (SDA/VSS)
IRQ_SHARED: J1.3, R3.2, U6.15 (~IRQ), U7.15 (~IRQ)
J10_RXD: J10.6, R6.2
J10_TXD: J10.3, R5.2
J11_RXD: J11.6, R8.2
J11_TXD: J11.3, R7.2
J12_RXD: J12.6, R10.2
J12_TXD: J12.3, R9.2
J13_RXD: J13.6, R12.2
J13_TXD: J13.3, R11.2
OSC_CLK: U6.6 (XTAL1), U7.6 (XTAL1), X1.3 (OUT)
SC_RESET_SHARED: C5.1, R4.2, U6.5 (~RESET), U7.5 (~RESET)
U2_CPN: C7.2, U2.3 (C1-)
U2_CPN2: C8.2, U2.5 (C2-)
U2_CPP: C7.1, U2.1 (C1+)
U2_CPP2: C8.1, U2.4 (C2+)
U2_RX232A: R6.1, U2.13 (R1IN)
U2_RX232B: R8.1, U2.8 (R2IN)
U2_TX232A: R5.1, U2.14 (T1OUT)
U2_TX232B: R7.1, U2.7 (T2OUT)
U2_VSN: C9.2, U2.6 (VS-)
U2_VSP: C9.1, U2.2 (VS+)
U3_CPN: C12.2, U3.3 (C1-)
U3_CPN2: C13.2, U3.5 (C2-)
U3_CPP: C12.1, U3.1 (C1+)
U3_CPP2: C13.1, U3.4 (C2+)
U3_RX232A: R10.1, U3.13 (R1IN)
U3_RX232B: R12.1, U3.8 (R2IN)
U3_TX232A: R9.1, U3.14 (T1OUT)
U3_TX232B: R11.1, U3.7 (T2OUT)
U3_VSN: C14.2, U3.6 (VS-)
U3_VSP: C14.1, U3.2 (VS+)
U6_RXA: U2.12 (R1OUT), U6.4 (RXA)
U6_RXB: U2.9 (R2OUT), U6.24 (RXB)
U6_TXA: U2.11 (T1IN), U6.3 (TXA)
U6_TXB: U2.10 (T2IN), U6.23 (TXB)
U7_RXA: U3.12 (R1OUT), U7.4 (RXA)
U7_RXB: U3.9 (R2OUT), U7.24 (RXB)
U7_TXA: U3.11 (T1IN), U7.3 (TXA)
U7_TXB: U3.10 (T2IN), U7.23 (TXB)

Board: 2 copper layers, 39 parts (0 on the bottom side), 44 nets, no tracks yet.
